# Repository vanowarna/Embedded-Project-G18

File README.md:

# LASER COMMUNICATION SYSTEM
## Embedded-Project-G18

<br>

### Table of Contents
1. [STABLE Code and Simulation File](/Code_Simulation_STABLE)
2. [Assembly scripts](/Code)
3. [Proteus simulation files](/Proteus%20simulation)
4. [PCB Design](/PCB%20Design)
5. [Documentation](/Documents)
6. [Evaluation video](/Documents/README.md)

<!-- #### Introduction
In Industrial applications, transmitting and receiving signals with higher precision and accuracy is the prime goal. For the embedded system project, we have designed a model to approach this using a laser beam. The system can transmit 4-bit simplex signals efficiently with a low-cost setup and display the received signal. To approach this, a transmitter and a receiver will be designed separately. For demonstration purposes, the transmitter is input with a 4-bit digital signal and the receiver displays the relevant signal. We aim to achieve this goal using two PIC16F84A microcontrollers for the hardware and Assembly language for scripting -->

#### Transmitter PCB
<table width="100%" border="0">
  <tr>    
  <td></td>
  <td></td>
  <td></td>
  </tr>
</table>

#### Receiver PCB
<table width="100%" border="0">
  <tr>    
  <td></td>
  <td></td>
  <td></td>
  </tr>
</table>

<br><br>

<br>

<br>

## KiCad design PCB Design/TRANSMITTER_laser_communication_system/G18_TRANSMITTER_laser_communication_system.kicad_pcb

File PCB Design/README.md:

### PCB Design 

#### KiCAD Files
- [Transmitter](/PCB%20Design/G18_RECEIVER_laser_communication_system)
- [Receiver](/PCB%20Design/G18_RECEIVER_laser_communication_system)

#### Gerber files
- [Transmitter](/PCB%20Design/GERBER/transmitter_UPDATED.zip)
- [Receiver](/PCB%20Design/GERBER/receiver_UPDATED.zip)

<!-- 

 -->

<table width="100%" border="0">
  <tr>    
  <td></td>
  <td></td>
  <td></td>
  </tr>
</table>

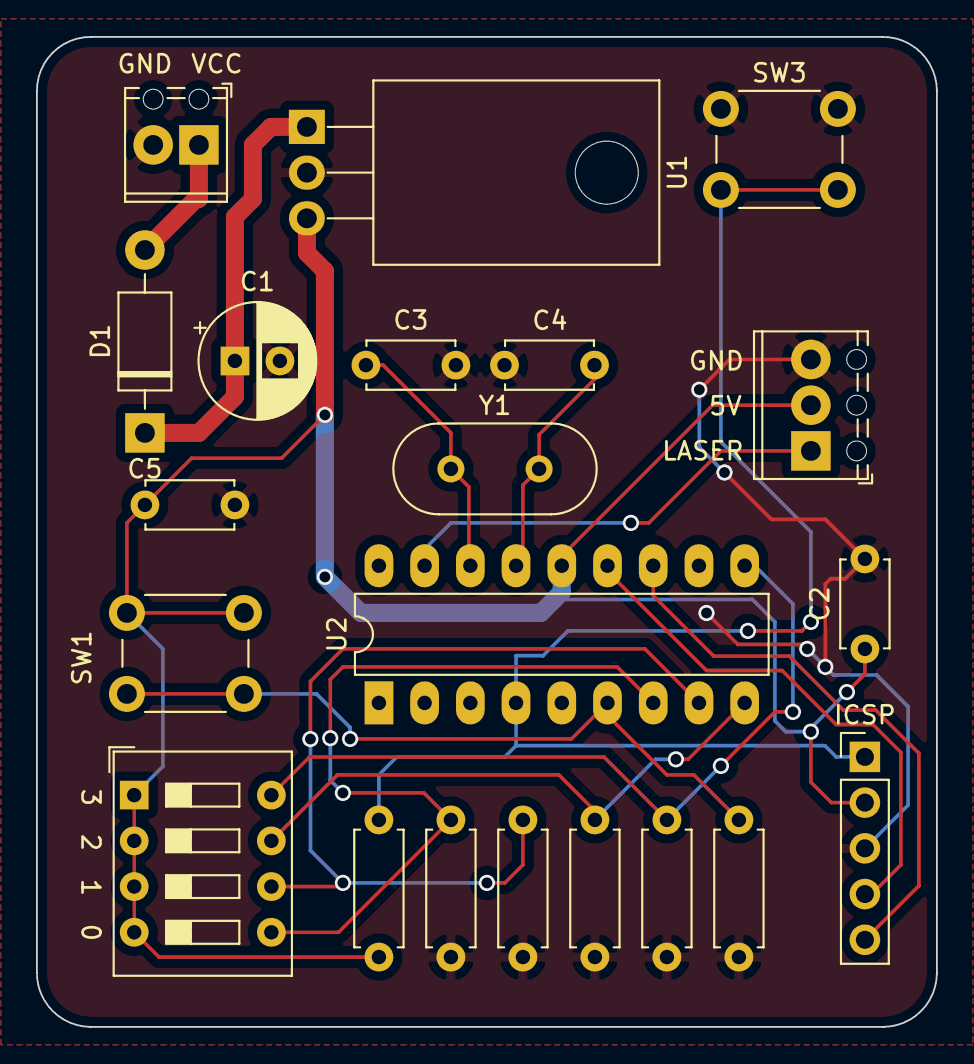
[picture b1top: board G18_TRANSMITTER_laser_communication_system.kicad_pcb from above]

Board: 2 copper layers, 50.0 x 55.0 mm, 21 parts (0 on the bottom side), 15 nets.

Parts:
C1: 100uF; CP_Radial_D6.3mm_P2.50mm
C2, C5: 0.1uF; C_Disc_D4.7mm_W2.5mm_P5.00mm
C3, C4: 22pF; C_Disc_D4.7mm_W2.5mm_P5.00mm
D1: 1N4007; D_DO-41_SOD81_P10.16mm_Horizontal
ICSP: Conn_01x05_Male; PinHeader_1x05_P2.54mm_Vertical
J1: Screw_Terminal_01x02; TerminalBlock_Phoenix_MPT-0,5-2-2.54_1x02_P2.54mm_Horizontal
J2: Screw_Terminal_01x03; TerminalBlock_Phoenix_MPT-0,5-3-2.54_1x03_P2.54mm_Horizontal
R1, R2, R3, R4, R5, R6: 10k; R_Axial_DIN0207_L6.3mm_D2.5mm_P7.62mm_Horizontal
SW1: Send_button; SW_PUSH_6mm_H4.3mm
SW2: SW_DIP_x04; SW_DIP_SPSTx04_Slide_9.78x12.34mm_W7.62mm_P2.54mm
SW3: Reset; SW_PUSH_6mm_H4.3mm
U1: L7805; TO-220-3_Horizontal_TabDown
U2: PIC16F84A-XXP; DIP-18_W7.62mm_LongPads
Y1: 4MHz; Crystal_HC18-U_Vertical

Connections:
5V: C2.1, C5.1, ICSP.2, J2.2, R6.2, SW1.1, SW2.1, SW2.2, SW2.3, SW2.4, U1.3, U2.14
BIT0: R2.1, SW2.8, U2.10
BIT1: R3.1, SW2.7, U2.9
BIT2: R4.1, SW2.6, U2.8
BIT3: R5.1, SW2.5, U2.7
CLOCK: ICSP.5, U2.12
DATA: ICSP.4, U2.13
GND: C1.2, C2.2, C3.2, C4.2, C5.2, ICSP.3, J1.2, J2.3, R1.2, R2.2, R3.2, R4.2, R5.2, SW3.1, U1.2, U2.5
LASER: J2.1, U2.17
MCLR: ICSP.1, R6.1, SW3.2, U2.4
unnamed: C1.1, D1.1, U1.1
unnamed: C3.1, U2.16, Y1.1
unnamed: C4.1, U2.15, Y1.2
unnamed: D1.2, J1.1
SEND: R1.1, SW1.2, U2.6

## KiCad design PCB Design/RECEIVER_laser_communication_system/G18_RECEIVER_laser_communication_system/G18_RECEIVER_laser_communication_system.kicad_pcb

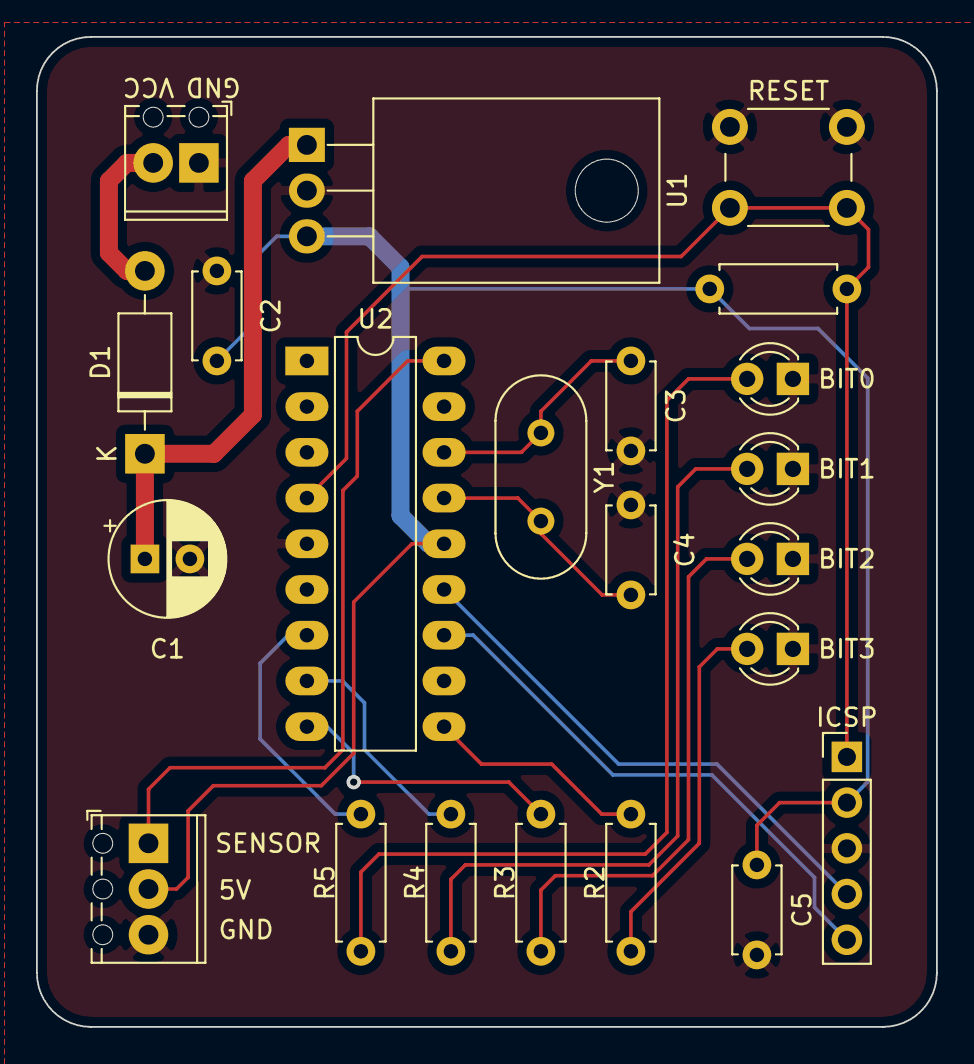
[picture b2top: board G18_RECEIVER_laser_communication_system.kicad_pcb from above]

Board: 2 copper layers, 50.0 x 55.0 mm, 22 parts (0 on the bottom side), 18 nets.

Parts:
BIT0, BIT1, BIT2, BIT3: LED; LED_D3.0mm
C1: 100uF; CP_Radial_D6.3mm_P2.50mm
C2, C5: 0.1uF; C_Disc_D4.7mm_W2.5mm_P5.00mm
C3, C4: 22pF; C_Disc_D4.7mm_W2.5mm_P5.00mm
D1: 1N4007; D_DO-41_SOD81_P10.16mm_Horizontal
ICSP: Conn_01x05_Male; PinHeader_1x05_P2.54mm_Vertical
J1: Screw_Terminal_01x02; TerminalBlock_Phoenix_MPT-0,5-2-2.54_1x02_P2.54mm_Horizontal
J2: Screw_Terminal_01x03; TerminalBlock_Phoenix_MPT-0,5-3-2.54_1x03_P2.54mm_Horizontal
R1: 10k; R_Axial_DIN0207_L6.3mm_D2.5mm_P7.62mm_Horizontal
R2, R3, R4, R5: 330; R_Axial_DIN0207_L6.3mm_D2.5mm_P7.62mm_Horizontal
RESET: Reset; SW_PUSH_6mm_H4.3mm
U1: L7805; TO-220-3_Horizontal_TabDown
U2: PIC16F84A-XXP; DIP-18_W7.62mm_LongPads
Y1: 4MHz; Crystal_HC18-U_Vertical

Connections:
5V: C2.1, C5.1, ICSP.2, J2.2, R1.1, U1.3, U2.14
BIT0: R5.2, U2.7
BIT1: R4.2, U2.8
BIT2: R3.2, U2.9
BIT3: R2.2, U2.10
CLOCK: ICSP.5, U2.12
DATA: ICSP.4, U2.13
GND: BIT0.1, BIT1.1, BIT2.1, BIT3.1, C1.2, C2.2, C3.2, C4.2, C5.2, ICSP.3, J1.1, J2.3, RESET.1, U1.2, U2.5
MCLR: ICSP.1, R1.2, RESET.2, U2.4
unnamed: C1.1, D1.1, U1.1
unnamed: C3.1, U2.16, Y1.1
unnamed: C4.1, U2.15, Y1.2
unnamed: D1.2, J1.2
unnamed: BIT3.2, R2.1
unnamed: BIT2.2, R3.1
unnamed: BIT1.2, R4.1
unnamed: BIT0.2, R5.1
SENSOR: J2.1, U2.18

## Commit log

2021-08-15 Created files
2021-08-15 Created two files
2021-08-15 test code
2021-08-15 Created blank file
2021-08-17 code v1.0
2021-08-17 Code v2.0
    - Still not working
    - Compiling OK
2021-08-20 Updated transmitter code
    Still not working
2021-08-20 Not working. Need to debug
2021-08-20 Rename Readme.md to Simulation_files.md
2021-08-20 Rename Simulation_files.md to Readme.md
2021-08-20 Test interrupt code Signed-off-by: vanowarna <55307326+vanowarna@users.noreply.github.com>
2021-08-20 Test proteus file
2021-08-20 Updated test file
2021-08-20 Delay 2 second added for visualization
2021-08-20 Corrected PORTA --> PORTB
2021-08-20 Added a missing BCF PORTA,0
2021-08-20 Created timing test v1.0
2021-08-20 Updated transmitter working code
2021-08-21 test update
2021-08-21 Created PCB files
2021-08-21 Added snapshots of the two boards
2021-08-21 PCB updated
2021-08-22 v2.0
2021-08-22 Invoice for the PCB fabrication
2021-09-13 Edit receiver added
2021-09-13 Extended delay
2021-09-19 DELAY changes - Added delay config file - Transmitter DELAY updated with 2 seconds
2021-09-19 Receiver delay updated - with 1 second
2021-09-19 Added 1 second delay
2021-09-19 Added receiver delay plan
2021-09-19 Working receiver code updated - Need to Test
2021-09-19 only transm.Verson.01
2021-09-19 Error corrected - Compiled without errors - Need to test
2021-09-19 Added CLRF STORE_INP
2021-09-19 Port B Cleared
2021-09-19 Code updated with corrected errors Signed-off-by: vanowarna <55307326+vanowarna@users.noreply.github.com>
2021-09-23 cleared STORE INP 50
2021-09-23 Protues sim file
2021-09-23 working codes - need testing
2021-09-23 Simulation file finalized
2021-09-23 Hex files - transmitter - receiver
2021-09-23 committed
2021-09-23 Added 0.5sec delay configuration in a text file - need to copy this to the code
2021-09-23 Speed changes
2021-09-23 Speed changes added
2021-09-23 Ptoreus final--working
2021-09-23 Added comments.
2021-09-23 Stable code
2021-09-23 Stable code and simulation file - Transmitter delay 2 second - Receiver delay 1 second - Proteus file --> STABLE
2021-09-23 Timing test file replaced
2021-09-23 Documentation for the Laser Communication system
2021-09-23 PCB Screenshots added for both modules
2021-09-23 Added PCB views to the Readme
2021-09-23 Images
2021-09-25 Added contributor information
2021-09-26 Added labels in the Simulation file
2021-09-27 Create LICENSE
2021-09-28 Added evaluation video
